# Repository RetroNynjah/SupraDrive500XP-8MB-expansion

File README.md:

# SupraDrive 500XP 8MB RAM expansion
The SupraDrive 500XP Hard Drive/RAM expansion for the Amiga 500 was available with 512kB, 1MB or 2MB's of RAM but it was expandable to 8MB of DRAM using 16 4x1Mbit DIL memory chips. Those chips were probably already pretty rare back then and they're totally unobtainable today.  
An adapter board was available(?) that made it possible to use 16 ZIP modules instead. I don't know if those modules were cheaper or more available back then but the adapter board probably didn't sell very well and is apparently very rare today, as are the ZIP modules.  
This is why I created this expansion board which can be populated with 16 4x1Mbit 20/26 pin SOJ chips. These chips existed from many manufacturers and can be scavenged from 4MB or 8MB 32-bit FPM SIMM modules which should still be quite easy to obtain.

## RAM chips ##

The DRAM chips that are needed for this module are Fast Page Mode (FPM) chips of 1M x 4 bits each (16pcs). The RAM package is SOJ-20.  
It's the kind that has the size of a 26 pin SOJ but are missing three pins in the middle on each side making them 20-pin.

They are available from many manufacturers with slight variantions in the part numbers. They typically include numbers like 514400, 414400 or 44400 such as MSM514400, HM514400, HY514400, HYB514400, NN514400, MN414400, AS4C14400, IBM014400, TMS44400  
Other FPM chips with the same specifications should probably work too:
MB814400, GM71C440, MT4C4001J, KM44C1000

The SupraDrive needs RAM with access times below 120ns. I have never seen SOJ FPM chips slower than that and most of them seem to be rated between 60ns and 80ns.

## Soldering ##
SOJ chips are best soldered using stencil and solder paste but I have made the pads extra long so they should be fairly easy to solder by hand too.
Except for the SOJ chips, the only components on the board are 100n 0603 SMD decoupling capacitors and some pin headers. I recommend the flat headers that often are sold at AliExpress and otherplaces as "Stackable Arduino headers" or "stackable female headers". 
Don't worry about the female part as it's only the bottom stacking part that we are interested in. Place the board correctly on top of the sockets and insert the stackable headers through the board and into the sockets, solder on the top side and cut off everything above the solder joint.  
The headers are sturdy but flexible and won't kill the sockets. Example: https://www.digikey.com/en/products/detail/adafruit-industries-llc/2830/5823439  
Round machined headers could work too but they are very fragile and easy to break if not properly aligned and there are plenty of pins to align.

## Testing ##
The SupraDrive has a dedicated memory test program on the SupraTools disk called SupraRamTest that works in a special test mode which is activated by setting DIP switch 5 to OFF (down position).  
My experience of SupraRamTest doesn't match the description in the instructions for the program. The instructions say that an 8MB board is tested in 4MB chunks and that it will ask if you want to test the upper 4MB. This doesn't happen for me.  
It also states that a complete pass will take five minutes but it takes much, much longer. On top of this it also identifies the 500XP as a 2MB RAM Card with 8MB of RAM. 
No matter what, I guess it's still very useful for testing the condition of the RAM chips.

I also like to test the memory using the excellent Amiga Test Kit utility by Keir Fraser: https://github.com/keirf/Amiga-Stuff  
This is done in normal memory mode with DIP switch 5 set to ON (up position). 

If you get errors during testing, refer to the RAM location layout below. 

Thanks too my friend Jani over at https://worldofjani.com/ for good discussions and testing. Here are his thoughts about this expansion: https://blog.worldofjani.com/?p=8064

## Installation ##
Installation is straightforward:
* Remove any old DIP chips
* Align the pins with the sockets
* Insert module
* Install all three jumpers J1, J2, J3 for 8 MB

There's an illustrated installation guide in the docs folder.

## Various links for SupraDrive 500XP ##
* https://bigbookofamigahardware.com/bboah/product.aspx?id=1246
* https://amiga.resource.cx/exp/supra500xp
* https://blog.worldofjani.com/?p=6808

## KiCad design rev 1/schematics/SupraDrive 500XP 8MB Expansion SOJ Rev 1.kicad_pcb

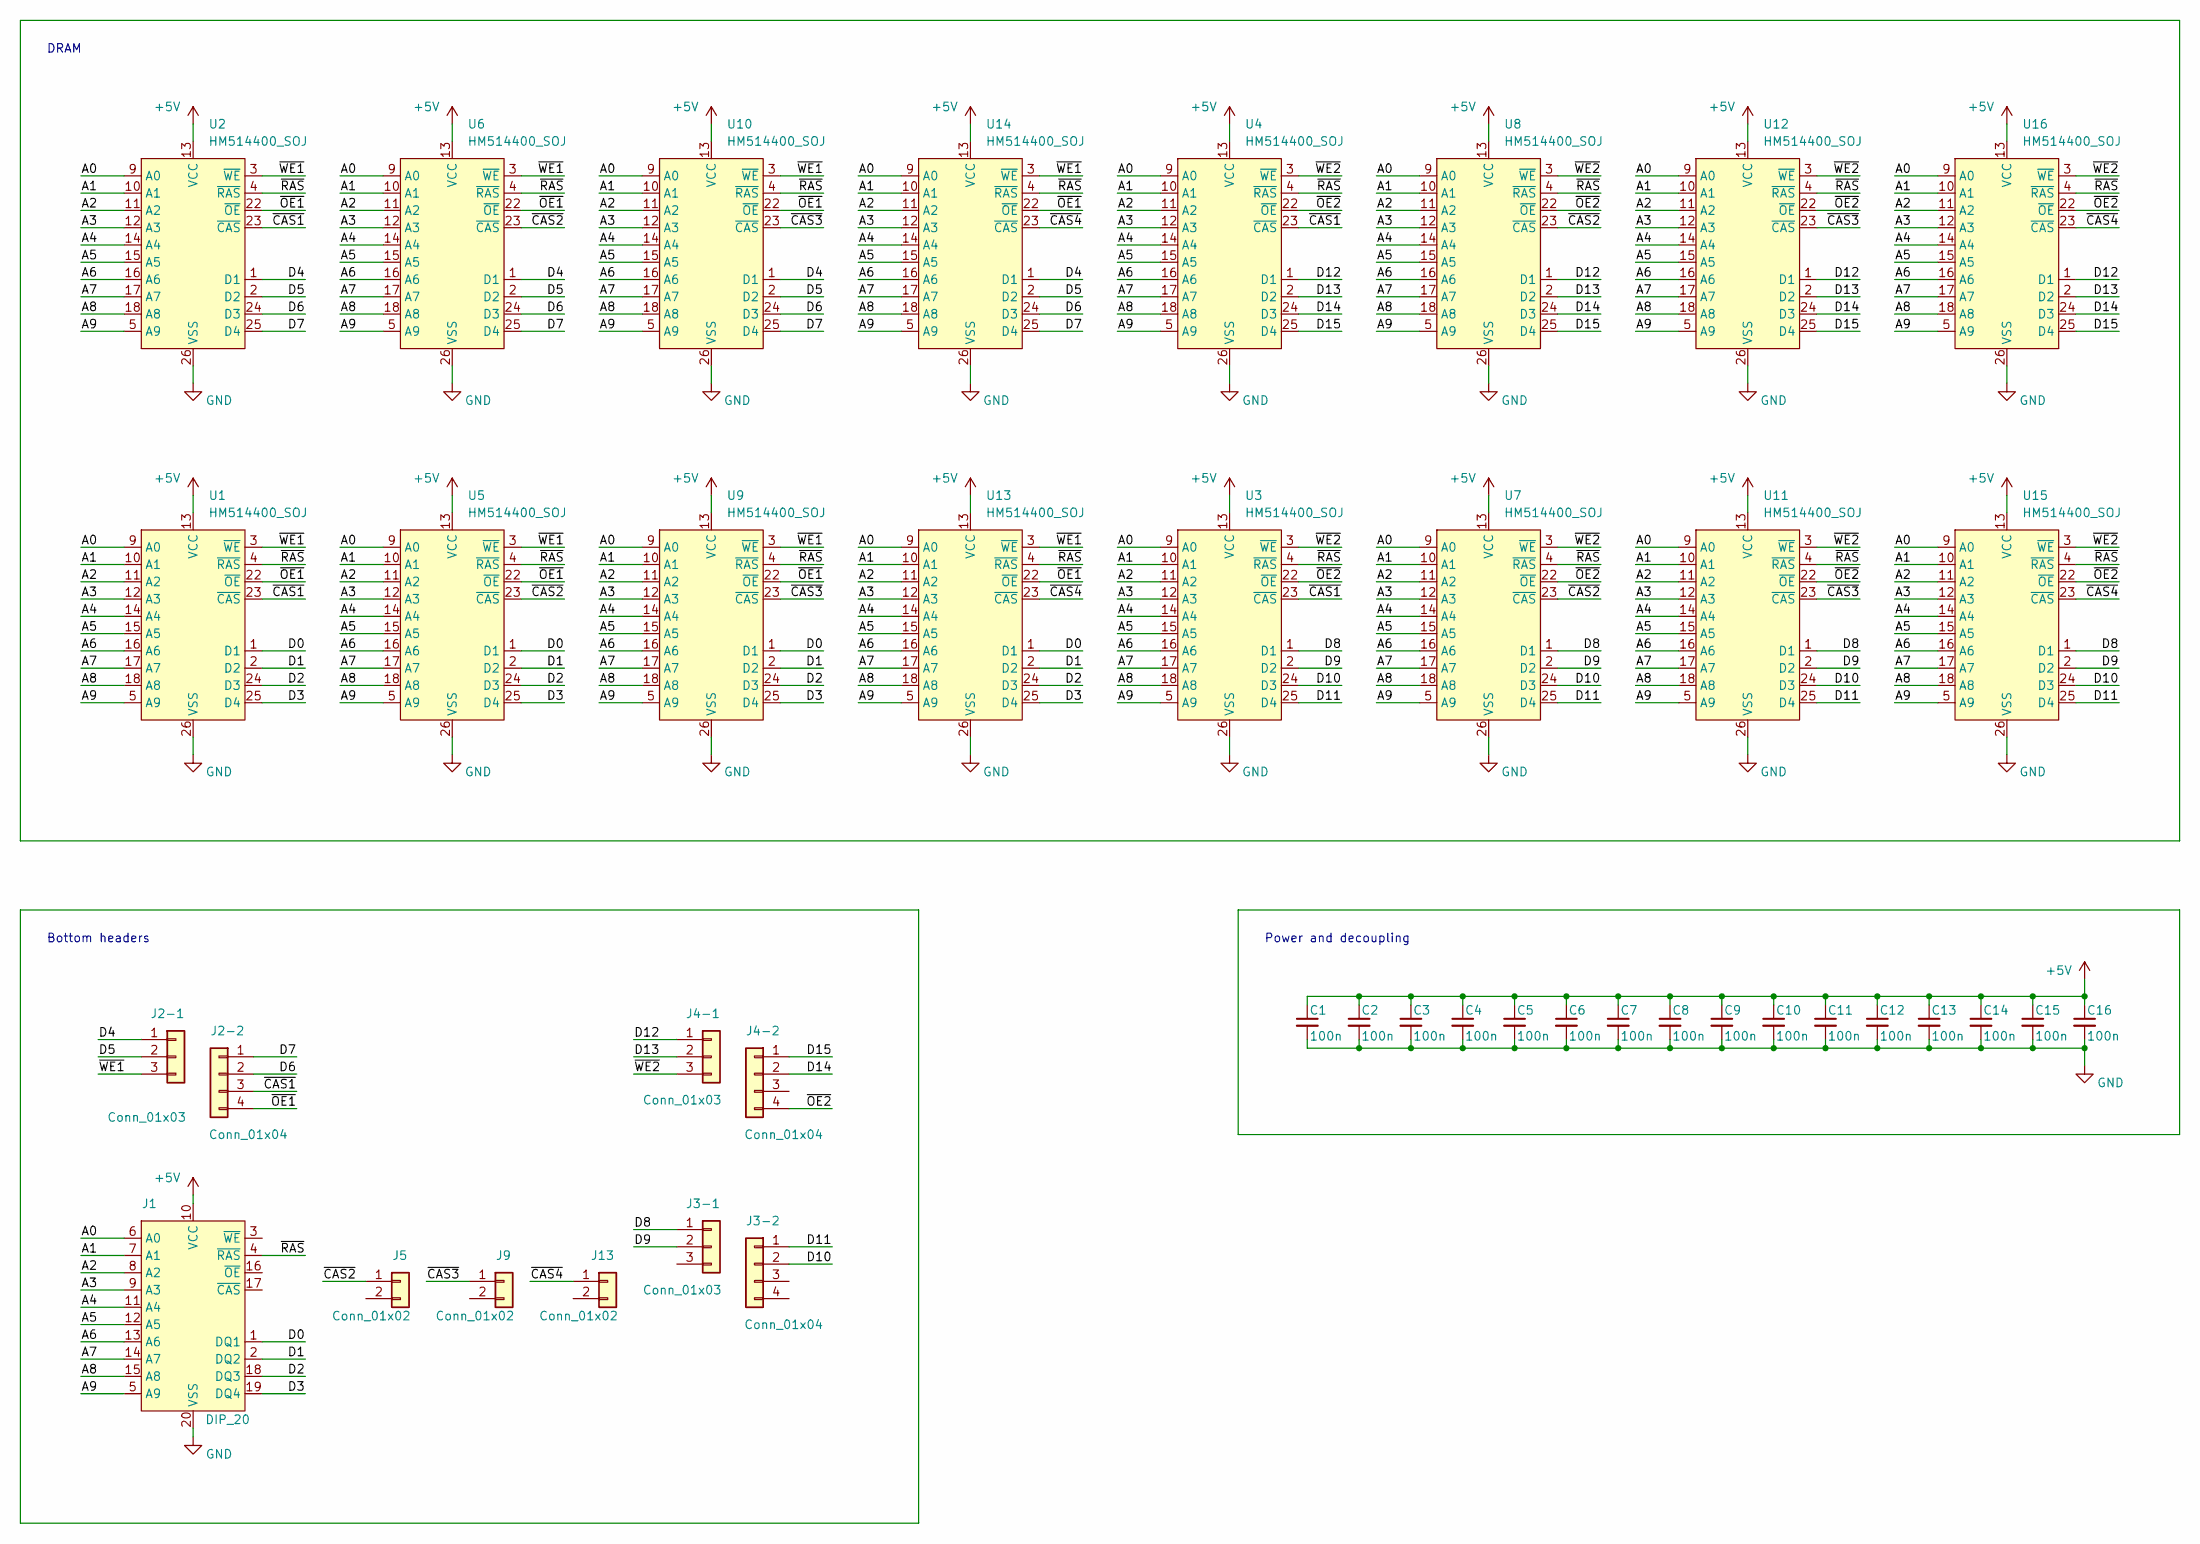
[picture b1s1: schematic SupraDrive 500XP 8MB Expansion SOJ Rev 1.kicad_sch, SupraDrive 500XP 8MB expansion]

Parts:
C1, C2, C3, C4, C5, C6, C7, C8, C9, C10, C11, C12, C13, C14, C15, C16: 100n; C_0603_1608Metric_Pad1.08x0.95mm_HandSolder
J1: DIP_20; DIP-20_W7.62mm_Down
J2-1, J3-1, J4-1: Conn_01x03; PinHeader_1x03_P2.54mm_Down_Pin1
J2-2, J3-2, J4-2: Conn_01x04; PinHeader_1x04_P2.54mm_Down
J5, J9, J13: Conn_01x02; PinHeader_1x02_P2.54mm_Down
U1, U2, U3, U4, U5, U6, U7, U8, U9, U10, U11, U12, U13, U14, U15, U16: HM514400_SOJ; SOJ-20-26_300mil

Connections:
+5V: C1.1, C2.1, C3.1, C4.1, C5.1, C6.1, C7.1, C8.1, C9.1, C10.1, C11.1, C12.1, C13.1, C14.1, C15.1, C16.1, J1.10 (VCC), U1.13 (VCC), U2.13 (VCC), U3.13 (VCC), U4.13 (VCC), U5.13 (VCC), U6.13 (VCC), U7.13 (VCC), U8.13 (VCC), U9.13 (VCC), U10.13 (VCC), U11.13 (VCC), U12.13 (VCC), U13.13 (VCC), U14.13 (VCC), U15.13 (VCC), U16.13 (VCC)
/A0: J1.6 (A0), U1.9 (A0), U2.9 (A0), U3.9 (A0), U4.9 (A0), U5.9 (A0), U6.9 (A0), U7.9 (A0), U8.9 (A0), U9.9 (A0), U10.9 (A0), U11.9 (A0), U12.9 (A0), U13.9 (A0), U14.9 (A0), U15.9 (A0), U16.9 (A0)
/A1: J1.7 (A1), U1.10 (A1), U2.10 (A1), U3.10 (A1), U4.10 (A1), U5.10 (A1), U6.10 (A1), U7.10 (A1), U8.10 (A1), U9.10 (A1), U10.10 (A1), U11.10 (A1), U12.10 (A1), U13.10 (A1), U14.10 (A1), U15.10 (A1), U16.10 (A1)
/A2: J1.8 (A2), U1.11 (A2), U2.11 (A2), U3.11 (A2), U4.11 (A2), U5.11 (A2), U6.11 (A2), U7.11 (A2), U8.11 (A2), U9.11 (A2), U10.11 (A2), U11.11 (A2), U12.11 (A2), U13.11 (A2), U14.11 (A2), U15.11 (A2), U16.11 (A2)
/A3: J1.9 (A3), U1.12 (A3), U2.12 (A3), U3.12 (A3), U4.12 (A3), U5.12 (A3), U6.12 (A3), U7.12 (A3), U8.12 (A3), U9.12 (A3), U10.12 (A3), U11.12 (A3), U12.12 (A3), U13.12 (A3), U14.12 (A3), U15.12 (A3), U16.12 (A3)
/A4: J1.11 (A4), U1.14 (A4), U2.14 (A4), U3.14 (A4), U4.14 (A4), U5.14 (A4), U6.14 (A4), U7.14 (A4), U8.14 (A4), U9.14 (A4), U10.14 (A4), U11.14 (A4), U12.14 (A4), U13.14 (A4), U14.14 (A4), U15.14 (A4), U16.14 (A4)
/A5: J1.12 (A5), U1.15 (A5), U2.15 (A5), U3.15 (A5), U4.15 (A5), U5.15 (A5), U6.15 (A5), U7.15 (A5), U8.15 (A5), U9.15 (A5), U10.15 (A5), U11.15 (A5), U12.15 (A5), U13.15 (A5), U14.15 (A5), U15.15 (A5), U16.15 (A5)
/A6: J1.13 (A6), U1.16 (A6), U2.16 (A6), U3.16 (A6), U4.16 (A6), U5.16 (A6), U6.16 (A6), U7.16 (A6), U8.16 (A6), U9.16 (A6), U10.16 (A6), U11.16 (A6), U12.16 (A6), U13.16 (A6), U14.16 (A6), U15.16 (A6), U16.16 (A6)
/A7: J1.14 (A7), U1.17 (A7), U2.17 (A7), U3.17 (A7), U4.17 (A7), U5.17 (A7), U6.17 (A7), U7.17 (A7), U8.17 (A7), U9.17 (A7), U10.17 (A7), U11.17 (A7), U12.17 (A7), U13.17 (A7), U14.17 (A7), U15.17 (A7), U16.17 (A7)
/A8: J1.15 (A8), U1.18 (A8), U2.18 (A8), U3.18 (A8), U4.18 (A8), U5.18 (A8), U6.18 (A8), U7.18 (A8), U8.18 (A8), U9.18 (A8), U10.18 (A8), U11.18 (A8), U12.18 (A8), U13.18 (A8), U14.18 (A8), U15.18 (A8), U16.18 (A8)
/A9: J1.5 (A9), U1.5 (A9), U2.5 (A9), U3.5 (A9), U4.5 (A9), U5.5 (A9), U6.5 (A9), U7.5 (A9), U8.5 (A9), U9.5 (A9), U10.5 (A9), U11.5 (A9), U12.5 (A9), U13.5 (A9), U14.5 (A9), U15.5 (A9), U16.5 (A9)
/D0: J1.1 (DQ1), U1.1 (D1), U5.1 (D1), U9.1 (D1), U13.1 (D1)
/D1: J1.2 (DQ2), U1.2 (D2), U5.2 (D2), U9.2 (D2), U13.2 (D2)
/D2: J1.18 (DQ3), U1.24 (D3), U5.24 (D3), U9.24 (D3), U13.24 (D3)
/D3: J1.19 (DQ4), U1.25 (D4), U5.25 (D4), U9.25 (D4), U13.25 (D4)
/D4: J2-1.1, U2.1 (D1), U6.1 (D1), U10.1 (D1), U14.1 (D1)
/D5: J2-1.2, U2.2 (D2), U6.2 (D2), U10.2 (D2), U14.2 (D2)
/D6: J2-2.2, U2.24 (D3), U6.24 (D3), U10.24 (D3), U14.24 (D3)
/D7: J2-2.1, U2.25 (D4), U6.25 (D4), U10.25 (D4), U14.25 (D4)
/D8: J3-1.1, U3.1 (D1), U7.1 (D1), U11.1 (D1), U15.1 (D1)
/D9: J3-1.2, U3.2 (D2), U7.2 (D2), U11.2 (D2), U15.2 (D2)
/D10: J3-2.2, U3.24 (D3), U7.24 (D3), U11.24 (D3), U15.24 (D3)
/D11: J3-2.1, U3.25 (D4), U7.25 (D4), U11.25 (D4), U15.25 (D4)
/D12: J4-1.1, U4.1 (D1), U8.1 (D1), U12.1 (D1), U16.1 (D1)
/D13: J4-1.2, U4.2 (D2), U8.2 (D2), U12.2 (D2), U16.2 (D2)
/D14: J4-2.2, U4.24 (D3), U8.24 (D3), U12.24 (D3), U16.24 (D3)
/D15: J4-2.1, U4.25 (D4), U8.25 (D4), U12.25 (D4), U16.25 (D4)
/~CAS1: J2-2.3, U1.23 (~CAS), U2.23 (~CAS), U3.23 (~CAS), U4.23 (~CAS)
/~CAS2: J5.1, U5.23 (~CAS), U6.23 (~CAS), U7.23 (~CAS), U8.23 (~CAS)
/~CAS3: J9.1, U9.23 (~CAS), U10.23 (~CAS), U11.23 (~CAS), U12.23 (~CAS)
/~CAS4: J13.1, U13.23 (~CAS), U14.23 (~CAS), U15.23 (~CAS), U16.23 (~CAS)
/~OE1: J2-2.4, U1.22 (~OE), U2.22 (~OE), U5.22 (~OE), U6.22 (~OE), U9.22 (~OE), U10.22 (~OE), U13.22 (~OE), U14.22 (~OE)
/~OE2: J4-2.4, U3.22 (~OE), U4.22 (~OE), U7.22 (~OE), U8.22 (~OE), U11.22 (~OE), U12.22 (~OE), U15.22 (~OE), U16.22 (~OE)
/~RAS: J1.4 (~RAS), U1.4 (~RAS), U2.4 (~RAS), U3.4 (~RAS), U4.4 (~RAS), U5.4 (~RAS), U6.4 (~RAS), U7.4 (~RAS), U8.4 (~RAS), U9.4 (~RAS), U10.4 (~RAS), U11.4 (~RAS), U12.4 (~RAS), U13.4 (~RAS), U14.4 (~RAS), U15.4 (~RAS), U16.4 (~RAS)
/~WE1: J2-1.3, U1.3 (~WE), U2.3 (~WE), U5.3 (~WE), U6.3 (~WE), U9.3 (~WE), U10.3 (~WE), U13.3 (~WE), U14.3 (~WE)
/~WE2: J4-1.3, U3.3 (~WE), U4.3 (~WE), U7.3 (~WE), U8.3 (~WE), U11.3 (~WE), U12.3 (~WE), U15.3 (~WE), U16.3 (~WE)
GND: C1.2, C2.2, C3.2, C4.2, C5.2, C6.2, C7.2, C8.2, C9.2, C10.2, C11.2, C12.2, C13.2, C14.2, C15.2, C16.2, J1.20 (VSS), U1.26 (VSS), U2.26 (VSS), U3.26 (VSS), U4.26 (VSS), U5.26 (VSS), U6.26 (VSS), U7.26 (VSS), U8.26 (VSS), U9.26 (VSS), U10.26 (VSS), U11.26 (VSS), U12.26 (VSS), U13.26 (VSS), U14.26 (VSS), U15.26 (VSS), U16.26 (VSS)

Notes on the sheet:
Power and decoupling
Bottom headers
DRAM

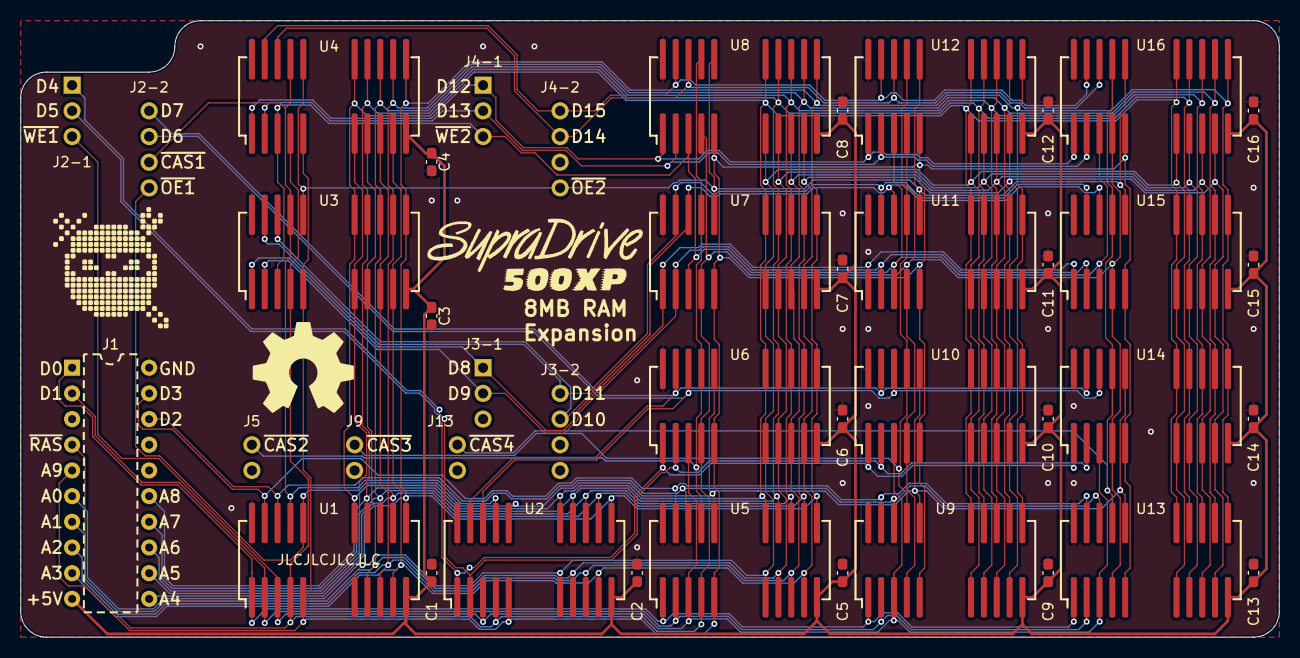
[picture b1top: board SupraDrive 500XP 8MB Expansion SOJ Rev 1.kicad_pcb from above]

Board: 2 copper layers, 124.5 x 61.0 mm, 42 parts (0 on the bottom side), 37 nets.

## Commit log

2024-05-06 Initial commit
    First upload of design
2025-02-25 RAM location maps
2025-02-25 Update README.md
    RAM location map
